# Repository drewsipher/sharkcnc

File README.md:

# SharkCNC

Open CNC control stack for a Sherline 2000 mill running FluidNC on an
ESP32-S3, with a PCB-milling-first workflow. Light enough for old laptops,
robust enough to trust over WiFi, and a CAM path that respects your time.

```
core/       C++20 library, no Qt: gcode parser, height-map warp,
            grbl/FluidNC driver + simulator, and the CAM engines
            (Gerber, Excellon, isolation, facing, outline, tool model)
app/        Qt6 desktop sender: 2D + 3D views, jog/DRO/console/run,
            probing, autolevel, integrated PCB CAM, tool library
tools/      sharkcam  - CLI CAM (iso / drill / face / outline / info)
            scnc-send - headless streamer (TCP or serial)
            scnc-sim  - fake FluidNC on a TCP port for development
hardware/   fluidnc-bob: the ESP32-S3 breakout board (KiCad)
tests/      41 unit + integration tests incl. driver<->simulator E2E
```

## Architecture in one line

The **PC** runs everything heavy (parsing, CAM, 3D, probing). The **ESP32**
only runs FluidNC and turns buffered G-code into step pulses. Nothing CAM- or
CAD-related ever touches the ESP — which is why a $6 chip drives the mill.

## Build

```sh
cmake --preset release        # add -DCMAKE_PREFIX_PATH=~/Qt/6.x/gcc_64 if
cmake --build build           # Qt lives outside the system paths
ctest --test-dir build
```

Qt 6 (Widgets + OpenGLWidgets) is only needed for the desktop app; `core/`
and `tools/` build without it. If the app aborts on launch with an xcb
plugin error, install `libxcb-cursor0` (or run with
`QT_QPA_PLATFORM=wayland`).

## Try it with zero hardware

```sh
./build/tools/scnc-sim 2323 &
./build/app/sharkcnc --tcp 127.0.0.1:2323
```

The simulator speaks real grbl protocol — status, flow control, jogging,
homing, `G38.2` probing against a fake warped surface, tool-change pauses —
so the whole workflow can be exercised on the couch.

## Views

- **2D** (default): fast QPainter top-down view, ideal for PCB. Copper
  overlay under isolation toolpaths, origin marker, scale bar. Pan-drag,
  wheel-zoom, double-click / **F** to fit.
- **3D** (Tab, or View menu): OpenGL, orbit / shift-drag pan / wheel zoom,
  **orthographic ↔ perspective** toggle, Top/Front/Iso presets (7/1/0).
  Load an STL (`File > Open STL`) to place stock or a part under the paths.

## PCB workflow (all in the CAM dock)

Export copper Gerber + Excellon drill from KiCad, then in the **PCB CAM**
panel:

| Tab | Does |
|---|---|
| **Copper (isolation)** | Gerber → isolation toolpaths. Pick a tool from the library; V-bits derive their cut width from the depth automatically. Live preview over the copper. |
| **Drill** | Excellon → drill G-code. Single-tool mode = one continuous job; multi-tool mode prompts you at each tool change. |
| **Face** | Raster / spiral surface flattening of a rectangular area, multi-pass. |
| **Outline** | Board cut-out offset by the tool radius, multi-pass, with N holding tabs so the board stays put. |

Each tab regenerates instantly as you change parameters, then **Load into
sender** and Run. Or headless:

```sh
sharkcam iso     front.gbr -o iso.nc  --tool 0.2 --passes 2
sharkcam drill   board.drl -o drill.nc
sharkcam face    -o face.nc    --w 60 --h 40 --tool 6 --depth 0.3
sharkcam outline -o cut.nc     --w 60 --h 40 --tabs 4
```

## Probing & autolevel

- **Z touch-off** (Probe menu): probe the surface, set Z zero with an
  optional plate-thickness offset.
- **Height map** (Probe menu): probe a serpentine grid over the board, then
  warp the loaded G-code so cuts follow the real (non-flat) surface — the
  thing that makes single-sided isolation reliable on warped FR4.

## Tool library

`Tools > Tool library`. Define end mills, ball noses, V-bits, chamfers,
drills — length, diameters, flutes, tip angle, corner radius, feeds/speeds.
The V-bit **cut-width-at-depth** number (shown live) is what isolation uses,
so choosing the tool + depth sets the trace clearance correctly. Persists to
the app config dir; the isolation tab picks from it.

## Streaming robustness

Motion is buffered inside FluidNC; the sender uses character-counting flow
control so the planner never starves. A network hiccup pauses the queue — it
cannot corrupt a running move. Tool changes (M0/M6) are handled host-side:
the sender drains motion, prompts you, and resumes on your click. Jobs can
also run from the controller's SD card with SharkCNC only supervising.

Status: M1 (sender) complete; M3 (probing/autolevel), M4 (PCB CAM: iso +
drill + outline), and M5 (facing, tool library) delivered. 3D view + STL
import done; STEP import and voxel cut-simulation are the next 3D items.
See [PLAN.md](PLAN.md). GPLv3-adjacent licensing TBD before v0.2.

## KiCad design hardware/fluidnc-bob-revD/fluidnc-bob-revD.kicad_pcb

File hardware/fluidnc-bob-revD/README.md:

# fluidnc-bob rev D — ESP32-S3 FluidNC breakout, external 5 V logic supply

Successor to the rev C board, folding in everything learned during the
2026-07-27 bench bring-up. **Deliverable = schematic + verified netlist +
footprint/3D assignments + DigiKey BOM.** Drew does the PCB layout
("Update PCB from Schematic" pulls everything in; footprints are from
KiCad's standard libraries with 3D models, plus the proven rev C devkit
socket footprint).

**Design state:** drawn-wire schematic (power symbols + real wires;
global labels only for long-haul nets) passes `kicad-cli sch erc` with
**0 violations**; netlist machine-verified against `generate/design.py`
(connectivity-partition + power-name diff); every footprint + 3D model
existence-checked against the installed KiCad 10 libraries (one
exception: the devkit socket uses the proven rev C custom footprint,
which has no 3D model). Each non-passive part carries hidden **Digikey**
and **Datasheet** URL properties. **Built and brought up 2026-08-06**:
FluidNC v4.0.4 **patched** (stock v4.0.4 crash-loops on S3 — see
`firmware/README.md`), config loads clean, board at `sharkcnc.local`.
Known rework on the built board: R40 (ZDIR series) was fabbed 1 k, fixed
to 100R in the schematic — swap the part on the board (1 k gives the
FMD2740C opto only ~3 mA).

**Devkit:** single 44-pin symbol + the rev C `ESP32_S3_DevKit_44_Socket`
footprint (copied into `fluidnc-bob-revD.pretty/`, socketed via two
PPTC221LFBN-RC strips). DigiKey-stocked spare: ESP32-S3-DEVKITC-1-N8
(identical pin legend; see BOM.md).

**Note:** the 74AHCT541 channel assignment differs from rev C (channels
follow devkit pad order so the schematic bus is crossing-free). This is
NOT internal to the board: it swapped the X and Z step/dir GPIOs and the
AUX/spindle GPIOs relative to rev C. The as-built map is in the table
below and in this directory's `config.yaml` (verified against both the
schematic netlist and the fabbed PCB pad nets).

## What changed vs rev C (and why)

1. **External 5 V logic supply into J1** (a separate regulated wall-wart,
   ~1 A) → fuse → TVS → +5 V rail. The rev D onboard 36 V→5 V buck
   (TSR 1-4850WI) was dropped: it was the priciest part (~$26 CAD) with no
   cheap 1 A / wide-input SIP equivalent, and the 36 V motor bus is
   transient-hostile (stepper regen) for a buck input. The steppers still
   run from the 36 V PSU directly, off-board. Bring-up fact that still
   applies: the devkit does NOT bridge USB power to its 5 V pin, so the
   board rail must always be supplied.
2. **Fuse (2 A) + SMBJ5.0A TVS** on the 5 V input. The TVS clamps
   overvoltage and, on a reverse-wired input, forward-conducts to blow the
   fuse before anything downstream sees reverse polarity (order spares).
   USB and board 5 V simultaneously is safe on this devkit (isolated).
3. **Single 5 V source** — the rev D `5V-SRC` jumper (JP1) and bench
   `5V-EXT` terminal (J12) are removed; with one external feed there is
   nothing to select. (Its footprint is free for a future ideal-diode
   P-FET if reverse protection without blowing F1 is ever wanted.)
4. **SN74AHCT541N at a full 5 V** — TTL V_IH (2 V) accepts the ESP's
   3.3 V directly; the rev C GS1A VCC-drop hack is gone. Step/dir
   outputs get **100 Ω series resistors**: ~9 mA per driver opto
   (mid-spec) and caps the buffer package current at ~54 mA (< 75 mA
   abs max) — rev C could exceed the rating with all channels lit.
5. **Driver ENABLE finally wired.** One shared enable pair on J4 pins
   4/5: +5 V (all ENA+ daisy-chained) and EN− (all ENA− daisy-chained
   into the Q2 sink, driven by GPIO9). Red LED2 lights when motors are
   disabled. FluidNC: `shared_stepper_disable_pin: gpio.9`.
6. **E-stop input on GPIO8**, conditioned like the limits (10 k pullup,
   1 k series, 100 nF). Wire an NC switch to GND. FluidNC v4:
   `control: estop_pin: gpio.8` — leave it commented out until J9 is
   wired (open input reads "pressed" → critical alarm at boot).
7. **Real connectors** (rev C was solder pads): Phoenix MKDS 5.08 screw
   terminals for power/drivers/spindle, Molex KK-254 (friction lock,
   crimp housings in the BOM) for limits/probe/E-stop/aux; SD keeps the
   rev C 2×6 header so the salvaged module plugs straight in.
10. **Onboard spindle relay** (Omron G5LE-14 DC5, SPDT 10 A/250 VAC,
   5 V coil) replaces the harvested off-board Songle. Q1 sinks the coil
   (S1M flyback); contacts COM/NO/NC on J10 switch the spindle's AC
   line. Wire the spindle through COM+NO so a dead board = spindle off.
8. **SD module runs from 3.3 V** (proven on the bench; keeps its level
   shifter below ESP-safe voltages).
9. **GPIO map mostly carried over from the fabbed rev C board**, but the
   crossing-free 74AHCT541 channel ordering (see note above) swapped
   X↔Z step/dir and AUX↔spindle. Limits, probe, and SD are unchanged.

## GPIO map (ESP32-S3, as-built — verified against PCB pad nets)

| Signal | GPIO | | Signal | GPIO |
|---|---|---|---|---|
| X step / dir | 7 / 6 | | X / Y / Z limit | 42 / 2 / 1 |
| Y step / dir | 16 / 15 | | Probe | 41 |
| Z step / dir | 18 / 17 | | **E-stop (new)** | **8** |
| Spindle relay | 4 | | SD CS / MOSI / SCK / MISO | 10 / 11 / 12 / 13 |
| Aux out | 5 | | **Stepper disable (new)** | **9** |

## FluidNC config

The full working config is `config.yaml` in this directory (flashed and
verified on the built board). Update it there and push to the board with
`curl -T config.yaml http://sharkcnc.local/flash/config.yaml`, then
`$Bye` to reload — serial XModem is unreliable on v4.0.4 (task_wdt log
spam corrupts the stream; large transfers crash the firmware).

## Connector wiring

| Ref | Type | Pins | Goes to |
|---|---|---|---|
| J1 | screw 2-pos | +5V, GND | external regulated 5 V supply (fused, TVS-protected) |
| J2 (X) | screw 5-pos | n/c, GND, XDIR, GND, XSTEP | FMD2740C X: DIR+→pin 3, SP+→pin 5, SP−+DIR− bridge→GND pin |
| J3 (Y) | screw 5-pos | GND, YDIR, GND, YSTEP, GND | FMD2740C Y: DIR+→pin 2, SP+→pin 4, SP−+DIR− bridge→GND pin |
| J4 (Z) | screw 5-pos | ZDIR, GND, ZSTEP, +5V, EN− | FMD2740C Z: DIR+→pin 1, SP+→pin 3; pins 4/5 = the **single shared** enable pair: daisy-chain ALL drivers' ENA+→pin 4 (+5V) and ENA−→pin 5 (EN−, Q2 sink — never wire ENA− to GND: enable opto stays energized = motors permanently disabled) |
| J5/J6/J7 | Molex KK-254 2 | SIG, GND | X / Y / Z limit switch (closes to GND) |
| J8 | Molex KK-254 2 | SIG, GND | probe |
| J9 | Molex KK-254 2 | SIG, GND | E-stop (NC to GND) |
| J10 | screw 3-pos | NO, COM, NC (COM center) | spindle AC switch: line hot → COM, spindle hot → NO; NC unused (planned: 2-pos COM+NO next rev) |
| J11 | Molex KK-254 2 | AUX, GND | spare buffered 5 V output (future spindle PWM) |
| J13 | header 2×6 | 5=3V3, 7=MISO, 8=MOSI, 9=SCK, 10=CS, 11/12=GND | salvaged microSD module — **same pad map as fabbed rev C** |

Driver interface is the bench-proven common-cathode sourcing: STEP→SP+,
DIR→DIR+, GND→SP−&DIR− bridge; step/dir stay **active high** in config
(same as rev C). EN unwired ⇒ enabled, so a rev C-style 3-wire hookup
still works before the EN lines are connected.

## ⚠ Layout checklist

1. The devkit socket footprint is the rev C one that already fits the
   fabbed board — no row-spacing gamble this time. Still check the
   devkit's printed pin legend against `DEVKIT_LEFT/RIGHT` in
   `generate/design.py` (pin 1 = 3V3, antenna end).
2. 5 V input nets (J1, F1, D1): keep F1 in series on J1.1 and the D1 TVS
   right at the connector; short/wide traces into the +5 V pour.
3. Local decoupling: C3/C4/C5 close to their loads (U1 VCC + devkit 5 V);
   keep the J1 input a few cm from the ESP antenna end.
4. Single-point ground at the supply; motor power never crosses the
   logic ground pour (same rule as rev C).
5. LED2/EN block near the driver terminals so the "MOTORS OFF" light is
   visible at the machine.
6. H1–H4 = M3 mounting holes, put one near each corner.
7. Power input: silk J1 clearly as **+5V / GND** — it is now a 5 V
   terminal, not 36 V. A reversed or over-voltage supply is caught only by
   F1 + D1, so keep that pair tight to the connector.
8. **MAINS on the RLY1/J10 corner.** Keep the relay contact traces and
   J10 in one corner, ≥ 6.4 mm creepage from ALL logic (slot the board
   under the relay if convenient), trace width ≥ 1 mm, no ground pour
   under the contact area. Coil side (pins 2/5) is logic — the relay
   body is the isolation barrier (4 kV impulse rated).

## Regenerating / verifying

```sh
python3 generate/design.py          # netlist dump + single-pad-net assert
python3 generate/gen_sch.py         # schematic (drawn wires + labels)
kicad-cli sch erc --exit-code-violations fluidnc-bob-revD.kicad_sch
python3 generate/verify_netlist.py  # diff KiCad netlist vs design.py
```

`generate/design.py` is the netlist source of truth **for the schematic
only** — once a board is fabbed, the `.kicad_pcb` becomes the pin
authority (rev C lesson, see `docs/HANDOFF.md`).

Ordering: import `digikey_bom.csv` at DigiKey (matches on MPN); details
and alternatives in `BOM.md`.

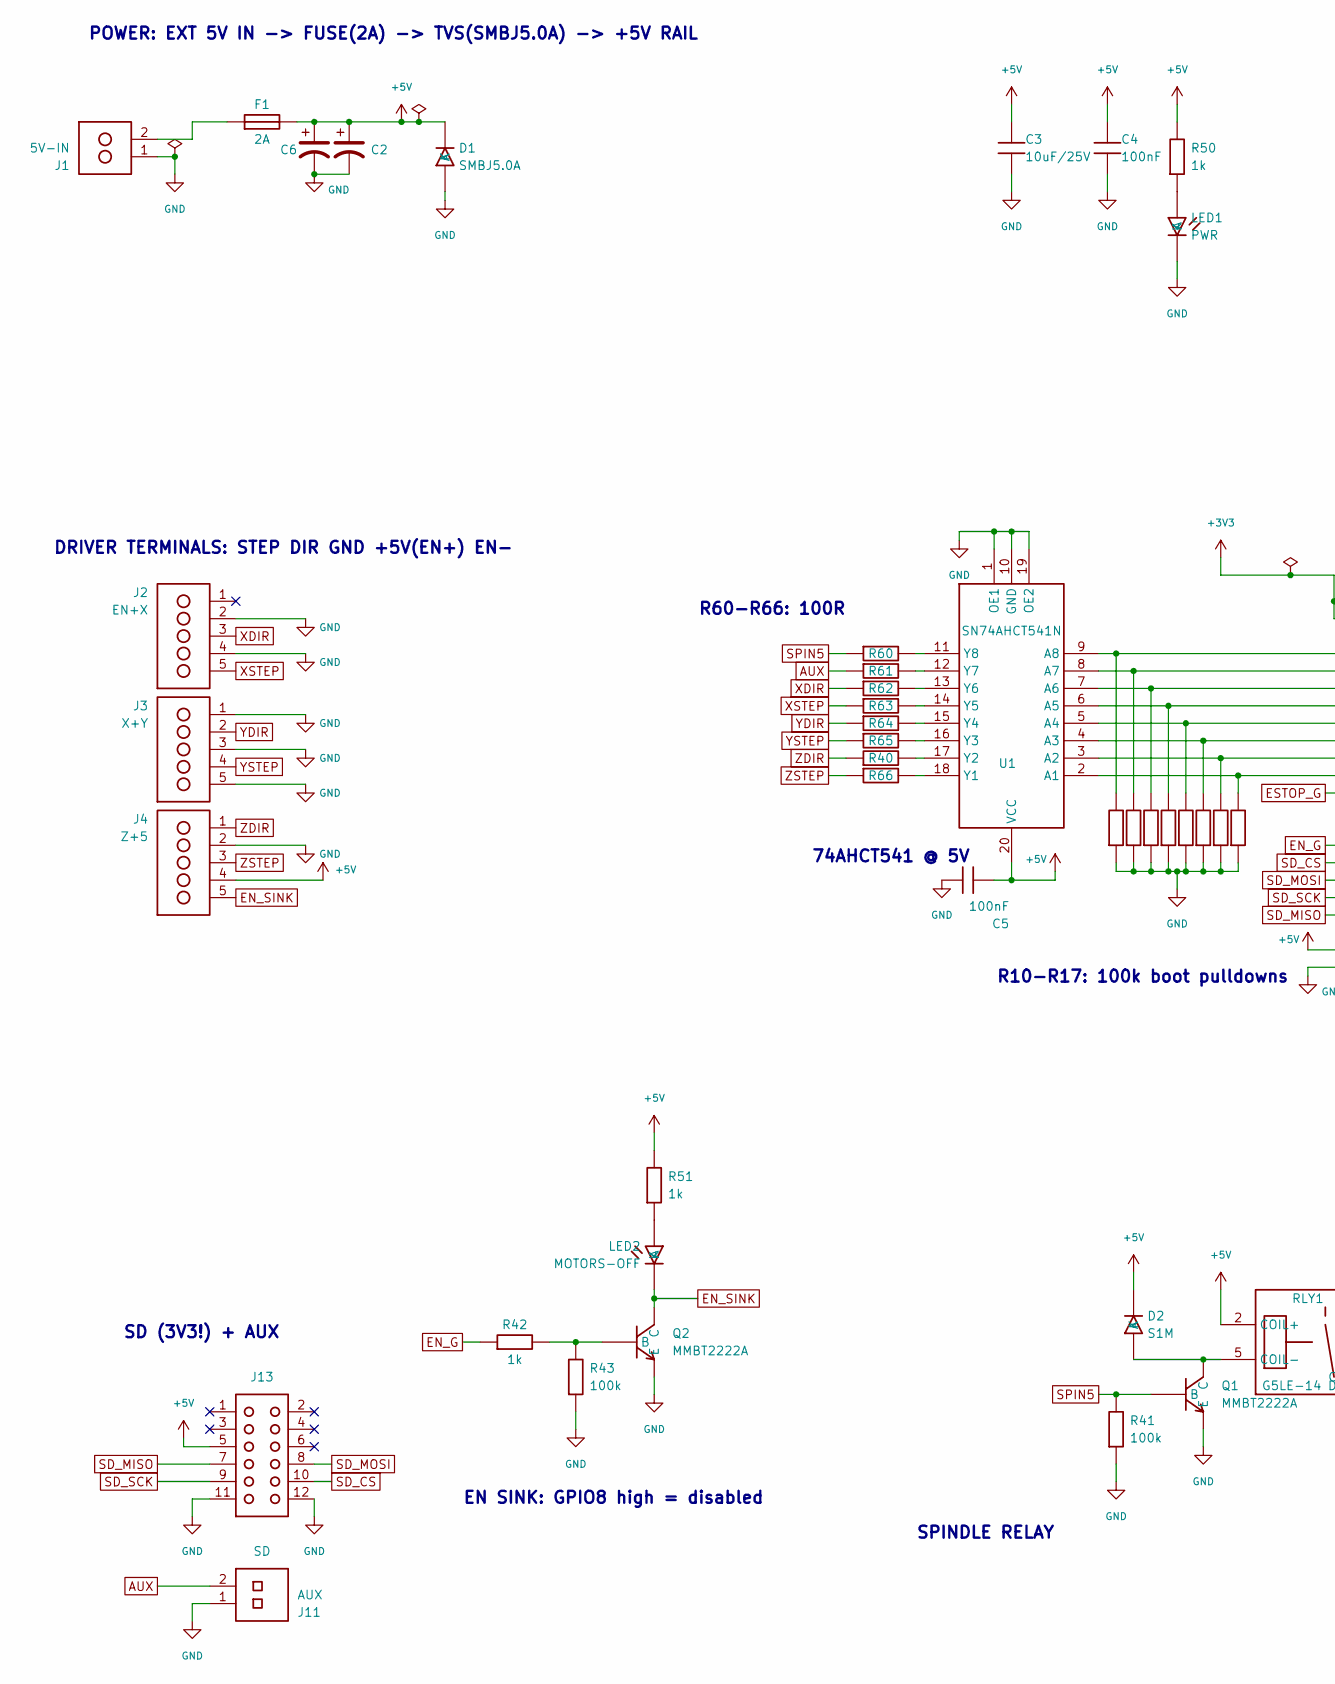
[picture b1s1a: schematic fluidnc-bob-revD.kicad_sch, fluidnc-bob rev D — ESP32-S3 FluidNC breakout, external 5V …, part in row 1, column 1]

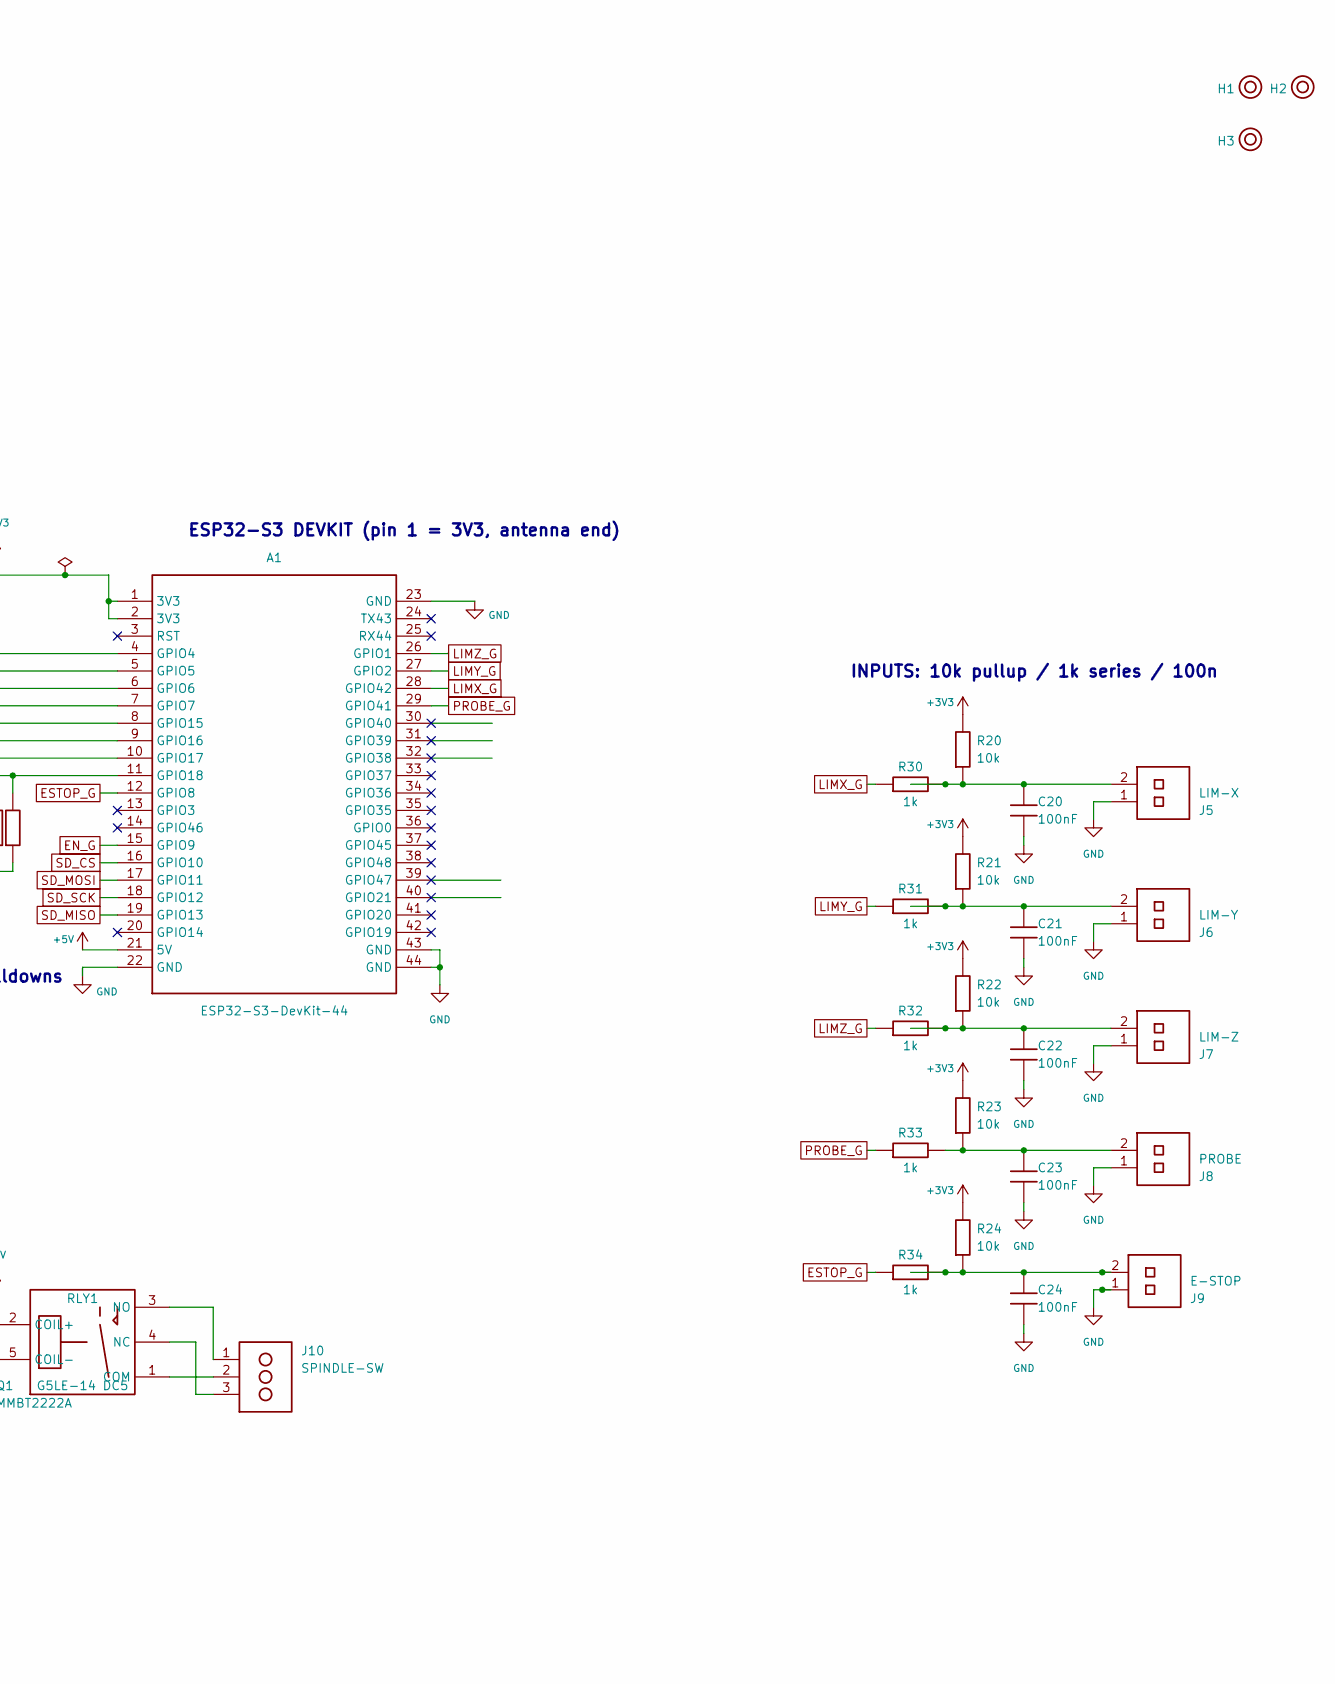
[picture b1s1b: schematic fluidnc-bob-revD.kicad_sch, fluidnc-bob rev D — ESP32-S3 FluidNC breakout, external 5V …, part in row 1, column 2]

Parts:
A1: ESP32-S3-DevKit-44; ESP32_S3_DevKit_44_Socket; Digikey 1965-ESP32-S3-DEVKITC-1-N8-ND
C2, C6: C_Polarized_US; CP_Radial_D8.0mm_P3.80mm
C3: 10uF/25V; C_1206_3216Metric
C4, C5, C20, C21, C22, C23, C24: 100nF; C_0805_2012Metric
D1: SMBJ5.0A; D_SMB; Digikey SMBJ5.0ALFCT-ND
D2: S1M; D_SMA; Digikey S1M-FDICT-ND
F1: 2A; Fuse_1206_3216Metric; Digikey F1457CT-ND
H1, H2, H3: M3; MountingHole_3.2mm_M3_Pad
J1: 5V-IN; TerminalBlock_Phoenix_MKDS-1,5-2-5.08_1x02_P5.08mm_Horizont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; Digikey 277-1263-ND
J2: EN+X; TerminalBlock_Phoenix_MKDS-1,5-5-5.08_1x05_P5.08mm_Horizont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; Digikey 277-13762-ND
J3: X+Y; TerminalBlock_Phoenix_MKDS-1,5-5-5.08_1x05_P5.08mm_Horizont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; Digikey 277-13762-ND
J4: Z+5; TerminalBlock_Phoenix_MKDS-1,5-5-5.08_1x05_P5.08mm_Horizont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; Digikey 277-13762-ND
J5: LIM-X; Molex_KK-254_AE-6410-02A_1x02_P2.54mm_Vertical; Digikey WM4200-ND
J6: LIM-Y; Molex_KK-254_AE-6410-02A_1x02_P2.54mm_Vertical; Digikey WM4200-ND
J7: LIM-Z; Molex_KK-254_AE-6410-02A_1x02_P2.54mm_Vertical; Digikey WM4200-ND
J8: PROBE; Molex_KK-254_AE-6410-02A_1x02_P2.54mm_Vertical; Digikey WM4200-ND
J9: E-STOP; Molex_KK-254_AE-6410-02A_1x02_P2.54mm_Vertical; Digikey WM4200-ND
J10: SPINDLE-SW; TerminalBlock_Phoenix_MKDS-1,5-3-5.08_1x03_P5.08mm_Horizont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; Digikey 277-1264-ND
J11: AUX; Molex_KK-254_AE-6410-02A_1x02_P2.54mm_Vertical; Digikey WM4200-ND
J13: SD; PinHeader_2x06_P2.54mm_Vertical; Digikey S2011EC-06-ND
LED1: PWR; LED_D5.0mm; Digikey 754-1263-ND
LED2: MOTORS-OFF; LED_D5.0mm; Digikey 754-1264-ND
Q1, Q2: MMBT2222A; SOT-23; Digikey MMBT2222A-FDICT-ND
R10, R11, R12, R13, R14, R15, R16, R17, R41, R43: 100k; R_0805_2012Metric
R20, R21, R22, R23, R24: 10k; R_0805_2012Metric
R30, R31, R32, R33, R34, R42, R50, R51: 1k; R_0805_2012Metric
R40, R60, R61, R62, R63, R64, R65, R66: 100R; R_0805_2012Metric
RLY1: G5LE-14 DC5; Relay_SPDT_Omron-G5LE-1; Digikey Z1011-ND
U1: SN74AHCT541N; DIP-20_W7.62mm_Socket; Digikey 296-4755-5-ND

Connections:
+3V3: A1.1 (3V3), A1.2 (3V3), R20.1, R21.1, R22.1, R23.1, R24.1
+5V: A1.21 (5V), C2.1, C3.1, C4.1, C5.2, C6.1, D1.1 (K), D2.1 (K), F1.2, J4.4, J13.5, R50.1, R51.1, RLY1.2 (COIL+), U1.20 (VCC)
AUX: J11.2, R61.1
EN_G: A1.15 (GPIO9), R42.1
EN_SINK: J4.5, LED2.1 (K), Q2.3 (C)
ESTOP_G: A1.12 (GPIO8), R34.1
GND: A1.22 (GND), A1.23 (GND), A1.43 (GND), A1.44 (GND), C2.2, C3.2, C4.2, C5.1, C6.2, C20.2, C21.2, C22.2, C23.2, C24.2, D1.2 (A), J1.1, J2.2, J2.4, J3.1, J3.3, J3.5, J4.2, J5.1, J6.1, J7.1, J8.1, J9.1, J11.1, J13.11, J13.12, LED1.1 (K), Q1.2 (E), Q2.2 (E), R10.2, R11.2, R12.2, R13.2, R14.2, R15.2, R16.2, R17.2, R41.2, R43.2, U1.1 (OE1), U1.10 (GND), U1.19 (OE2)
LIMX_G: A1.28 (GPIO42), R30.1
LIMY_G: A1.27 (GPIO2), R31.1
LIMZ_G: A1.26 (GPIO1), R32.1
unnamed: A1.4 (GPIO4), R10.1, U1.9 (A8)
unnamed: A1.5 (GPIO5), R11.1, U1.8 (A7)
unnamed: A1.6 (GPIO6), R12.1, U1.7 (A6)
unnamed: A1.7 (GPIO7), R13.1, U1.6 (A5)
unnamed: A1.8 (GPIO15), R14.1, U1.5 (A4)
unnamed: A1.9 (GPIO16), R15.1, U1.4 (A3)
unnamed: A1.10 (GPIO17), R16.1, U1.3 (A2)
unnamed: A1.11 (GPIO18), R17.1, U1.2 (A1)
unnamed: C20.1, J5.2, R20.2, R30.2
unnamed: C21.1, J6.2, R21.2, R31.2
unnamed: C22.1, J7.2, R22.2, R32.2
unnamed: C23.1, J8.2, R23.2, R33.2
unnamed: C24.1, J9.2, R24.2, R34.2
unnamed: D2.2 (A), Q1.3 (C), RLY1.5 (COIL-)
unnamed: F1.1, J1.2
unnamed: LED1.2 (A), R50.2
unnamed: LED2.2 (A), R51.2
unnamed: Q2.1 (B), R42.2, R43.1
unnamed 28: J10.2, RLY1.1 (COM); also elsewhere on the board
unnamed 29: J10.3, RLY1.4 (NC); also elsewhere on the board
unnamed 30: J10.1, RLY1.3 (NO); also elsewhere on the board
unnamed: R66.2, U1.18 (Y1)
unnamed: R40.2, U1.17 (Y2)
unnamed: R65.2, U1.16 (Y3)
unnamed: R64.2, U1.15 (Y4)
unnamed: R63.2, U1.14 (Y5)
unnamed: R62.2, U1.13 (Y6)
unnamed: R61.2, U1.12 (Y7)
unnamed: R60.2, U1.11 (Y8)
PROBE_G: A1.29 (GPIO41), R33.1
SD_CS: A1.16 (GPIO10), J13.10
SD_MISO: A1.19 (GPIO13), J13.7
SD_MOSI: A1.17 (GPIO11), J13.8
SD_SCK: A1.18 (GPIO12), J13.9
SPIN5: Q1.1 (B), R41.1, R60.1
XDIR: J2.3, R62.1
XSTEP: J2.5, R63.1
YDIR: J3.2, R64.1
YSTEP: J3.4, R65.1
ZDIR: J4.1, R40.1
ZSTEP: J4.3, R66.1

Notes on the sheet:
EN SINK: GPIO8 high = disabled
INPUTS: 10k pullup / 1k series / 100n
SPINDLE RELAY
74AHCT541 @ 5V
SD (3V3!) + AUX
R60-R66: 100R
DRIVER TERMINALS: STEP DIR GND +5V(EN+) EN-
POWER: EXT 5V IN -> FUSE(2A) -> TVS(SMBJ5.0A) -> +5V RAIL
ESP32-S3 DEVKIT (pin 1 = 3V3, antenna end)
R10-R17: 100k boot pulldowns

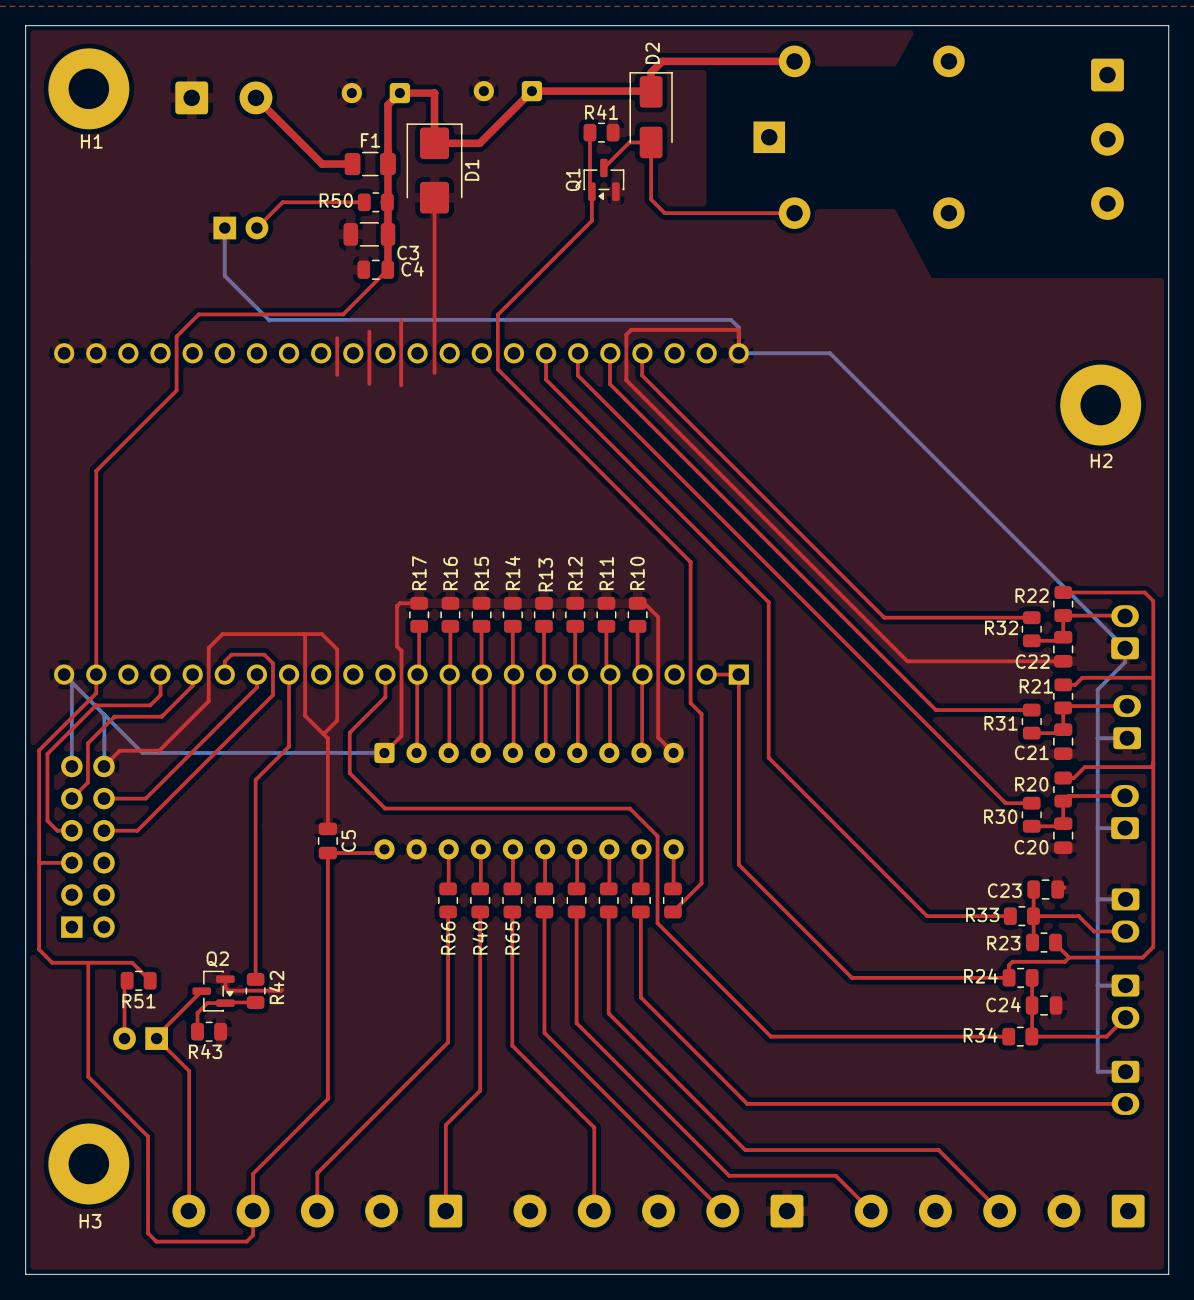
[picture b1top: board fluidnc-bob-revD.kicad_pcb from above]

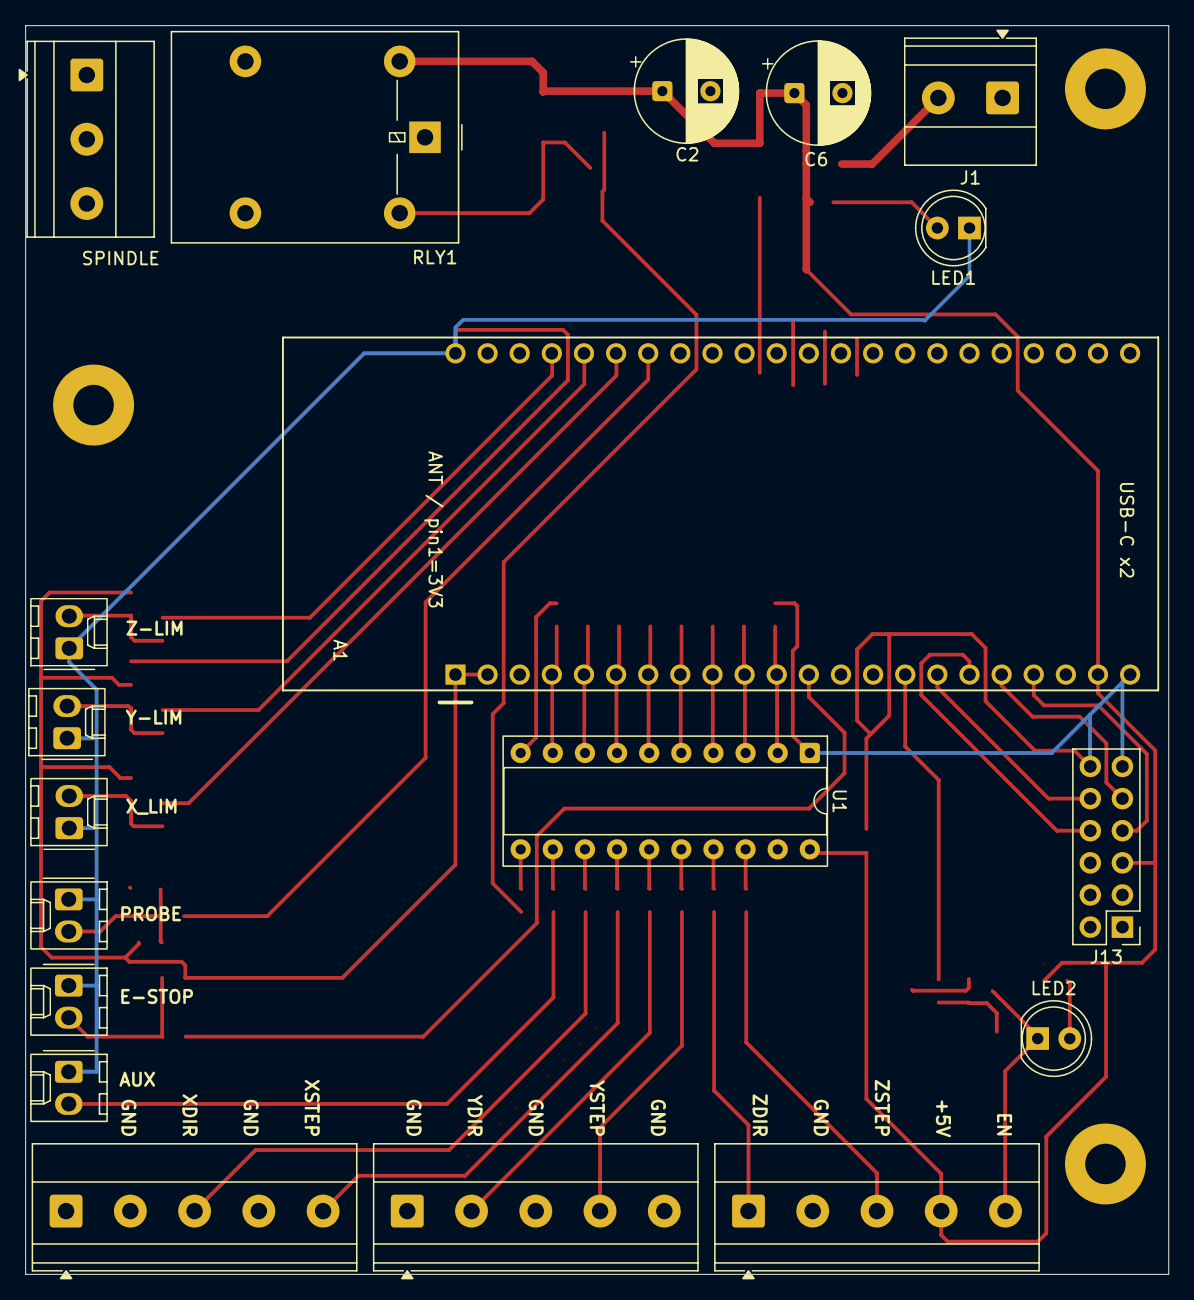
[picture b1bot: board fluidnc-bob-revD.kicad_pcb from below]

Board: 2 copper layers, 90.4 x 98.7 mm, 66 parts (19 on the bottom side), 51 nets.

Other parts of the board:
SPINDLE: SPINDLE-SW; TerminalBlock_Phoenix_MKDS-1,5-3-5.08_1x03_P5.08mm_Horizont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

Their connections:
unnamed 28: SPINDLE.2; also elsewhere on the board
unnamed 29: SPINDLE.3; also elsewhere on the board
unnamed 30: SPINDLE.1; also elsewhere on the board

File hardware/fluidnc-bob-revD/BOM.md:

# fluidnc-bob rev D BOM

Import `digikey_bom.csv` into DigiKey's BOM Manager (myLists → upload) —
it matches on Manufacturer Part Number; the Digi-Key Part Number column is
filled where it was explicitly verified. Quantities include spares.

**Verified on DigiKey (product page confirmed, in stock as of 2026-07-27):**
buffer, fuse, socket strips, Phoenix terminal blocks. Jellybean
passives/discretes use industry-standard MPNs.

**Power:** the board runs from a **separate regulated 5 V wall-wart supply
(~1 A)** wired into J1 — NOT included in this BOM (Drew supplies it). The
rev D onboard 36 V→5 V buck (TSR 1-4850WI) was removed: it was the single
priciest part (~$26 CAD) with no cheap 1 A / wide-input equivalent. The
36 V motor PSU still feeds the stepper drivers directly, off-board.

## Semiconductors & modules

| Ref | Part | MPN | DK PN | Qty (order) | Alternatives |
|---|---|---|---|---|---|
| U1 | Octal buffer, TTL-in, DIP-20 | **SN74AHCT541N** (TI) | 296-4755-5-ND | 2 | Nexperia 74HCT541N; TI SN74HCT541N |
| Q1, Q2 | NPN, SOT-23 | **MMBT2222A-7-F** (Diodes) | — | 10 | onsemi MMBT2222ALT1G |
| D1 | TVS 5 V standoff, SMB | **SMBJ5.0A** (Littelfuse) | — | 5 | Vishay SMBJ5.0A-E3/52 — clamps the 5 V rail and crowbars a reverse-wired input (blows F1) |
| D2 | Flyback 1 A 1000 V, SMA | **S1M-13-F** (Diodes) | — | 10 | onsemi S1M; any 1N4007-class SMA |
| LED1 | 5 mm green | **WP7113GD** (Kingbright) | — | 5 | any 5 mm LED |
| LED2 | 5 mm red | **WP7113ID** (Kingbright) | — | 5 | any 5 mm LED |
| F1 | Fuse 2 A 63 V, 1206 | **0466002.NR** (Littelfuse) | F1457CT-ND | 5 | Bourns SF-1206F200-2 (verified) |
| RLY1 | Relay SPDT 10 A/250 VAC, 5 V coil | **G5LE-14 DC5** (Omron) | Z1011-ND (page verified) | 2 | TE OJ-SH-105LMH; the harvested Songle SRD-05VDC is the same class |

## Passives (0805 unless noted)

| Ref | Value | MPN | Qty (order) |
|---|---|---|---|
| R10–R17, R41, R43 | 100 kΩ | RC0805FR-07100KL (Yageo) | 20 |
| R20–R24 | 10 kΩ | RC0805FR-0710KL | 20 |
| R30–R34, R40, R42, R50, R51 | 1 kΩ | RC0805FR-071KL | 20 |
| R60–R66 | 100 Ω | RC0805FR-07100RL | 20 |
| C4, C5, C20–C24 | 100 nF 50 V X7R | CL21B104KBCNNNC (Samsung) | 20 |
| C3 | 10 µF 25 V X7R, 1206 | CL31B106KAHNNNE (Samsung) | 5 |

## Connectors

| Ref | Part | MPN | DK PN | Qty (order) |
|---|---|---|---|---|
| (A1) | Socket strip 1×22, 2.54 mm ×2 | **PPTC221LFBN-RC** (Sullins) | — (page verified) | 3 |
| J1 | Screw terminal 2-pos 5.08 (5 V in) | **1715721** (Phoenix MKDS 1,5/2-5,08) | — (page verified) | 2 |
| J10 | Screw terminal 3-pos 5.08 | **1715734** (Phoenix MKDS 1,5/3-5,08) | — (page verified) | 2 |
| J2–J4 | Screw terminal 5-pos 5.08 | **1715750** (Phoenix MKDS 1,5/5-5,08) | — (page verified) | 4 |
| J5–J9, J11 | Molex KK-254 header 2-pos, friction lock | **22-23-2021** (Molex) | — (mfr page verified) | 8 |
| — | KK-254 housing 2-pos w/ ramp | **22-01-3027** (Molex) | — (mfr page verified) | 10 |
| — | KK-254 crimp terminal (2759 series, 22–30 AWG) | 08-50-0114 (Molex) | — | 50 |
| J13 | Pin header 2×6, 2.54 mm (SD module, rev C pad map) | PRPC006DAAN-RC (Sullins) | — | 2 |
| (U1) | DIP-20 socket | — on hand (optional) | — | — |

Crimp-shy alternative for the KK inputs: pre-crimped KK/2759-series
leads (search "Molex KK 254 pre-crimped 22AWG") — the board side is
identical. J13 mates with the salvaged SD module's existing 2×6 cable
(pad map identical to the fabbed rev C board: 5=3V3, 7=MISO, 8=MOSI,
9=SCK, 10=CS, 11/12=GND, rest NC).

## Devkit (A1)

The board sockets the existing 44-pin dual-USB-C ESP32-S3 clone using the
rev C custom socket footprint (proven fit). The official Espressif board
has the identical pin legend and is DigiKey-stocked if you want a spare:
**ESP32-S3-DEVKITC-1-N8** ([product page](https://www.digikey.com/en/products/detail/espressif-systems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
— N8 = no PSRAM, which is fine (FluidNC doesn't need it; GPIO 35-37 are
then free). Verify its header row spacing against the socket before
soldering a board around it.

## Not ordered (on hand / off-board)

- ESP32-S3-WROOM-1 N16R8 44-pin dual-USB-C devkit (existing)
- microSD breakout module (salvaged, fed 3.3 V via J13 pin 5)
- M3 standoffs/screws (H1–H4)

## Electrical sanity notes

- Opto drive: AHCT541 at 5 V through 100 Ω into FMD2740C (~270 Ω internal
  + LED): ≈ 9 mA per input — mid-spec (5–15 mA), matches the proven rev C
  drive topology.
- Worst-case buffer package current: 6 ch × 9 mA ≈ 54 mA < 75 mA abs max.
- 5 V supply sizing: devkit WiFi bursts ≈ 350 mA + buffer 55 mA + SD
  100 mA + relay coil ≈ 80 mA + LEDs ≈ 600 mA peak, ~300 mA typical → a
  regulated **5 V / 1 A** wall-wart is comfortable (2 A gives headroom).
- Relay contacts (J10 COM/NO/NC) switch the spindle's AC line: 10 A /
  250 VAC rating vs the Sherline's ~1.5 A draw. Mains lives ONLY on the
  RLY1-contact / J10 corner — see the layout checklist.
- 5 V input protection (J1 → F1 → D1): F1 (2 A) is overcurrent; D1
  (SMBJ5.0A, 5 V standoff) clamps overvoltage AND, if the input is
  reverse-wired, forward-conducts to blow F1 before anything downstream
  sees reverse polarity — that's why F1 gets spares. (A dedicated
  ideal-diode P-FET was considered; the fuse + TVS crowbar is simpler and
  sufficient for a regulated wall-wart source — see README.)

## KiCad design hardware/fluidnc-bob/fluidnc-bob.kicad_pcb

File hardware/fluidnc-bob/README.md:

# fluidnc-bob rev C — ESP32-S3 FluidNC breakout (schematic + netlist)

FluidNC controller interface for the Sherline 2000 / FMD2740C drivers:
socketed **44-pin dual-USB-C ESP32-S3-WROOM-1 (N16R8)** devkit, SN74HC541N
5 V buffer (VCC dropped through a GS1A so 3.3 V inputs meet V_IH), filtered
limit/probe inputs, microSD breakout header, spindle relay driver.
All connections are **solder wire pads** — no connectors.

**Deliverable = schematic + verified netlist + footprint assignments.**
Board layout is done by hand in KiCad ("Update PCB from Schematic" pulls in
everything, including the custom footprints in `fluidnc-bob.pretty/`).

**Design state:** ERC clean (0 violations); netlist machine-verified
against `generate/design.py` (`generate/verify_netlist.py` — partition and
power-net comparison). Unbuilt, rev C.

## ⚠ Layout-time checklist

1. **MEASURE THE DEVKIT ROW SPACING.** The socket footprint assumes
   **22.86 mm (0.9")**; both 22.86 and 25.4 mm exist among 44-pin S3 boards.
   Set `ROWSP` in `generate/gen_fp.py` (or edit the footprint) to match, and
   check the devkit's printed pin legend against `DEVKIT_LEFT/RIGHT` in
   `generate/design.py` (pin 1 = 3V3, antenna end).
2. N16R8 (octal PSRAM): GPIO 35/36/37 intentionally unconnected.
3. U1's buffer channels are interchangeable — permute freely during routing.
4. Keep the FMD2740C signal runs and logic ground away from motor power;
   single-point ground at the supply.
5. Don't feed 5 V and devkit USB simultaneously unless the devkit's
   backfeed diode is verified.

## Wire pad groups

| Ref | Pads (1 = square) | Goes to |
|---|---|---|
| J1 | 5V, GND | 5 V PSU (through F1 polyfuse, D2 reverse crowbar) |
| J2 | STEP, DIR, GND | X driver: SP+, DIR+; GND wire bridges SP−+DIR− |
| J3 | STEP, DIR, GND | Y driver |
| J4 | STEP, DIR, GND | Z driver |
| J5 / J6 | SIG, GND | X / Y limit switch (closes to GND) |
| J10 / J11 | SIG, GND | Z limit / probe |
| J7 | +5V, COIL− | spindle relay coil (2N7000 low side, D1 flyback) |
| J8 | AUX, GND | spare buffered 5 V output |
| J9 | SCK, MISO, MOSI, CS, 5V, GND | microSD breakout (feed it 5 V; its 4050 + 3.3 V reg handle the rest) |

## GPIO map (ESP32-S3)

| Signal | GPIO | | Signal | GPIO |
|---|---|---|---|---|
| X step / dir | 18 / 17 | | X / Y / Z limit | 42 / 2 / 1 |
| Y step / dir | 16 / 15 | | Probe | 41 |
| Z step / dir | 7 / 6 | | SD SCK / MISO / MOSI / CS | 12 / 13 / 11 / 10 |
| Spindle relay | 5 | | Aux out | 4 |

Inputs: 10 k pullup to 3V3 + 1 k series + 100 nF on board.

## FluidNC config

The maintained config is [`config.yaml`](config.yaml) (bench bring-up,
as-built active-high step/dir; limits/probe are `:low` because the board
pulls them up and switches close to GND). Verified against FluidNC
v4.0.3 example syntax — note it is `sdcard:`, not `sd:`.

If the drivers are reworked to common-anode (SP+/DIR+ tied to +5V),
add `:low` to every `step_pin` and `direction_pin`.

Upload jobs to SD and run locally — WiFi then carries only status/jog and
can never stall a cut. Verify pin syntax against the FluidNC wiki for the
S3 release you flash.

## Regenerating / verifying

```sh
python3 generate/gen_fp.py        # footprints (socket ROWSP lives here)
python3 generate/gen_sch.py       # schematic (drawn wires; self-checks)
kicad-cli sch erc --exit-code-violations fluidnc-bob.kicad_sch
python3 generate/verify_netlist.py  # diff KiCad netlist vs design.py
```

`generate/design.py` is the netlist source of truth. `generate/gen_pcb.py`
is retired (the rev B auto-layout experiment) — kept for reference only;
it no longer matches the current design.

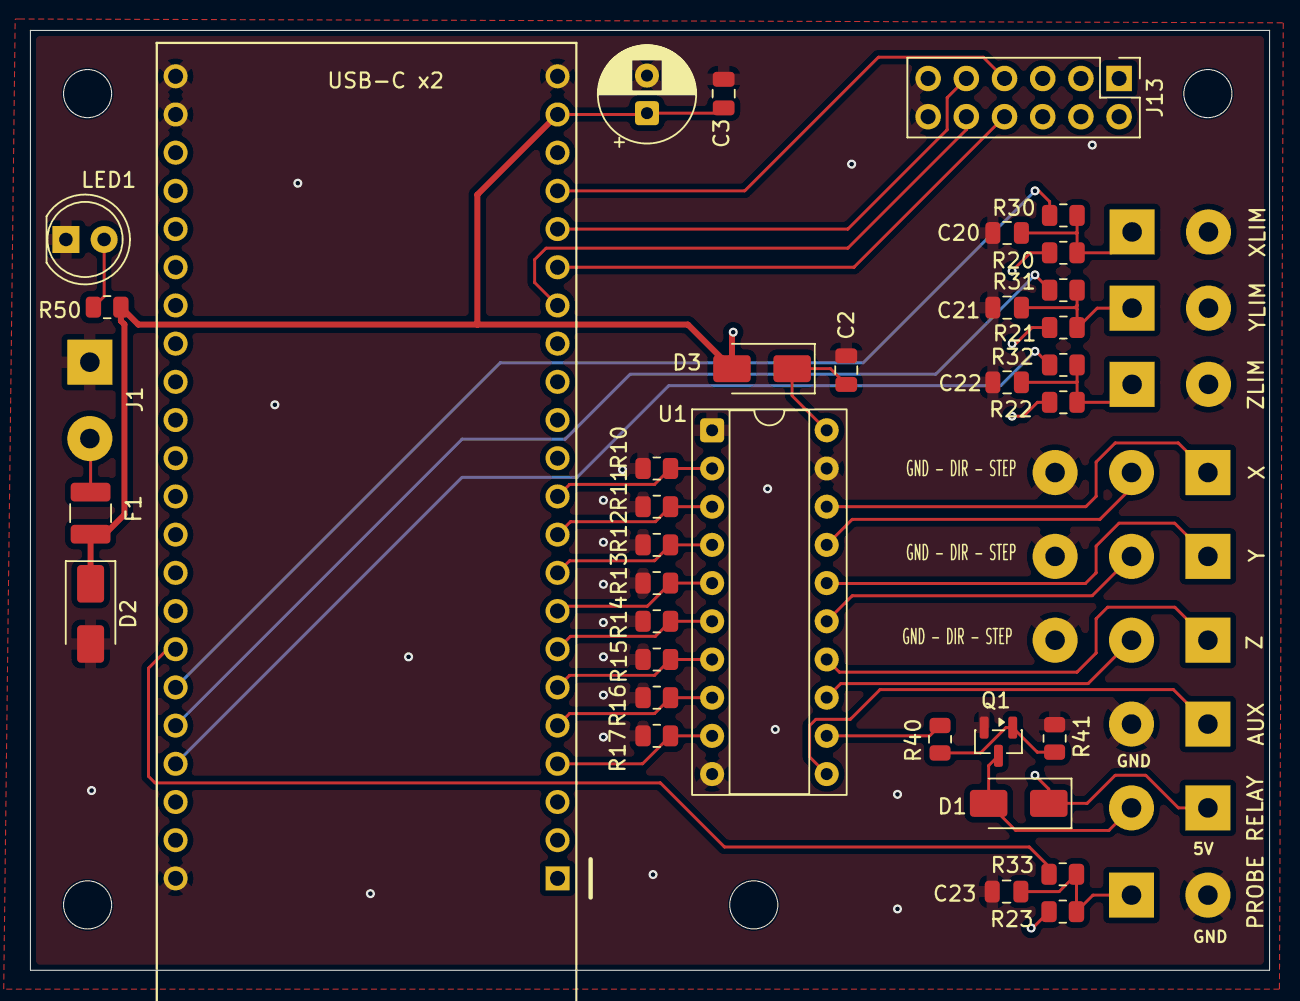
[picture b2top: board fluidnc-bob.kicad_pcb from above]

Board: 4 copper layers, 82.4 x 62.5 mm, 49 parts (0 on the bottom side), 36 nets.

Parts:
A1: ESP32-S3-DevKit-44; ESP32_S3_DevKit_44_Socket
AUX: AUX; WirePads_1x02_P5.08mm
C1: 100uF; CP_Radial_D6.3mm_P2.50mm
C2, C3, C20, C21, C22, C23: 100nF; C_0805_2012Metric
D1, D2, D3: GS1A; D_SMA
F1: 1210L150/16WR; Fuse_1210_3225Metric
H1, H2, H3, H4: MountingHole; MountingHole_3.2mm_M3
J1: 5V-IN; WirePads_1x02_P5.08mm
J13: Conn_02x06_Odd_Even; PinHeader_2x06_P2.54mm_Vertical
LED1: PWR; LED_D5.0mm
PROBE: PROBE; WirePads_1x02_P5.08mm
Q1: MMBT2222A; SOT-23
R10, R11, R12, R13, R14, R15, R16, R17, R41: 100k; R_0805_2012Metric
R20, R21, R22, R23: 10k; R_0805_2012Metric
R30, R31, R32, R33, R40, R50: 1k; R_0805_2012Metric
RELAY: RELAY; WirePads_1x02_P5.08mm
U1: SN74HC541N; DIP-20_W7.62mm_Socket
X: X-DRV; WirePads_1x03_P5.08mm
XLIM: LIM-X; WirePads_1x02_P5.08mm
Y: Y-DRV; WirePads_1x03_P5.08mm
YLIM: LIM-Y; WirePads_1x02_P5.08mm
Z: Z-DRV; WirePads_1x03_P5.08mm
ZLIM: LIM-Z; WirePads_1x02_P5.08mm

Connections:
+3V3: A1.1 (3V3), R20.1, R21.1, R22.1, R23.1
+5V: A1.21 (5V), C1.1, C3.1, D1.1 (K), D2.1 (K), D3.2 (A), F1.2, J13.5, R50.1, RELAY.1
AUX1: AUX.1, U1.11 (Y8)
CS: A1.16 (GPIO10), J13.10
GND: A1.22 (GND), A1.23 (GND), A1.43 (GND), A1.44 (GND), AUX.2, C1.2, C2.1, C3.2, C20.2, C21.2, C22.2, C23.2, D2.2 (A), J1.1, J13.11, J13.12, LED1.1 (K), PROBE.2, Q1.2 (E), R10.2, R11.2, R12.2, R13.2, R14.2, R15.2, R16.2, R17.2, R41.2, U1.1 (OE1), U1.10 (GND), U1.19 (OE2), X.3, XLIM.2, Y.3, YLIM.2, Z.3, ZLIM.2
MISO: A1.19 (GPIO13), J13.7
MOSI: A1.17 (GPIO11), J13.8
unnamed: A1.26 (GPIO1), R32.2
unnamed: A1.27 (GPIO2), R31.2
unnamed: A1.4 (GPIO4), R17.1, U1.9 (A8)
unnamed: A1.5 (GPIO5), R16.1, U1.8 (A7)
unnamed: A1.6 (GPIO6), R15.1, U1.7 (A6)
unnamed: A1.7 (GPIO7), R14.1, U1.6 (A5)
unnamed: A1.8 (GPIO15), R13.1, U1.5 (A4)
unnamed: A1.9 (GPIO16), R12.1, U1.4 (A3)
unnamed: A1.10 (GPIO17), R11.1, U1.3 (A2)
unnamed: A1.11 (GPIO18), R10.1, U1.2 (A1)
unnamed: A1.29 (GPIO41), R33.2
unnamed: A1.28 (GPIO42), R30.2
unnamed: C20.1, R20.2, R30.1, XLIM.1
unnamed: C21.1, R21.2, R31.1, YLIM.1
unnamed: C22.1, R22.2, R32.1, ZLIM.1
unnamed: C23.1, PROBE.1, R23.2, R33.1
unnamed: D1.2 (A), Q1.3 (C), RELAY.2
unnamed: F1.1, J1.2
unnamed: LED1.2 (A), R50.2
unnamed: Q1.1 (B), R40.2, R41.1
SCK: A1.18 (GPIO12), J13.9
SPIN5: R40.1, U1.12 (Y7)
VCC_BUF: C2.2, D3.1 (K), U1.20 (VCC)
XDIR: U1.17 (Y2), X.2
XSTEP: U1.18 (Y1), X.1
YDIR: U1.15 (Y4), Y.2
YSTEP: U1.16 (Y3), Y.1
ZDIR: U1.13 (Y6), Z.2
ZSTEP: U1.14 (Y5), Z.1

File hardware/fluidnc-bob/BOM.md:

# fluidnc-bob rev C BOM — everything from Drew's bins

| Qty | Ref | Part | Notes |
|---|---|---|---|
| 1 | A1 | ESP32-S3-WROOM-1 N16R8 devkit, 44-pin dual USB-C | on hand |
| 2 | (A1) | 1×22 female header, 2.54 mm | cut from stock female headers |
| 1 | U1 | SN74HC541N, DIP-20 | on hand (×3); VCC fed via D3 |
| 1 | (U1) | DIP-20 socket | optional, if in the bin |
| 3 | D1, D2, D3 | MCC GS1A, DO-214AC (SMA) | flyback / reverse crowbar / VCC drop |
| 9 | R10–R17, R41 | 100 kΩ 0805 | boot-time pulldowns + gate bleed |
| 4 | R20–R23 | 10 kΩ 0805 | input pullups |
| 6 | R30–R33, R40, R50 | 1 kΩ 0805 | series / gate / LED |
| 6 | C2, C3, C20–C23 | 100 nF 0805 | |
| 1 | C1 | 100 µF ≥16 V electrolytic THT, 2.5 mm | on hand |
| 1 | Q1 | MMBT2222A SOT-23 | relay driver (standard B-E-C SOT-23 pinout) |
| 1 | F1 | Littelfuse 1210L150/16WR PTC polyfuse, 1210 (1.5 A hold) | self-resetting; D2 crowbar trips it on reverse polarity |
| 1 | LED1 | 5 mm LED | power indicator |
| — | J1–J11 | solder wire pads (on the PCB) | no connectors: wires solder in |
| 1 | — | microSD breakout (74HC4050 + 3.3 V reg type) | on hand; wires to J9, feed 5 V |
| 4 | H1–H4 | M3 screw + standoff | |

Only possible purchase: a DIP-20 socket (optional).
